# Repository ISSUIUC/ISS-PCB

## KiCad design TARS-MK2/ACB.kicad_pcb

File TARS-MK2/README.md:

# TARS-MK2

> Don't let me leave Murph!\
> -Matthew McConaughey

# TODO

## FCB:
- [ ] Finalize overall component locations and begin trace layout
- [ ] Add RFM95!
- [ ] Make appropriate connections to b2b (board-to-board) MLPlus connectors
- [x] Copy MCU_AC design to MCU_HYBRID
- [ ] Add connectors for pressure transducers (MPLUS 3pos?)

TODO for the MCU specifically:
- [x] Associate certain MIMX pins with T4.1 pins so connections match with MK1 design
- [ ] think about pull-up/down resistors on communication busses
- [ ] add test points for power-up sequence observation (for debugging)
- [ ] Think about MCU-MCU communication lines
- [ ] Figure out exactly which peripherals are available with chip-on-board that weren't on the T4.1
- [ ] Add I2C/UART (+SPI?) expansion ports
- [ ] Should MCUs be powered by 3V3 or 5V?
- [ ] SAM-M8Q?
- [x] Additional IMU? (Maybe MPU9250 or BMI160 look nice)

TODO for MPU:
- [x] Talk to Octavo systems and see if they can review our design on short notice
- [ ] Implement the boot configuration pins according the to C-SiP design manual
- [ ] Break out necessary I2C and SPI busses
- [x] Keep USB host connector (probably not)

## ACB:
  - [ ] Attempt to replace the SODIMM connector with a lower profile one
  - [ ] Add debug LEDS
  - [ ] Add UART port for console and debugging

## POWER:
  - [ ] Add MLPlus b2b connectors
  - [ ] Power ON LEDs!!
  - [ ] Add a ground plane (both sides)
  - [ ] Consider switching SMD footprints for mosfet and voltage regulator
  - [ ] Are XT60s going to fit (switch to XT30s? JST-XH?)

## COTS:
  - [x] Finalize layout of components.
  - [x] Add MLPlus b2b connectors
  - [x] Add MLPlus ejection charge/switch connectors

---

### Schematic Hierarchy:
- `TARS-MK2.sch`: Consolidated root schematic
  - `Power.sch`: Power management and charging schematic
    - In redesign
  - `COTS.sch`: Commercial altimeter system schematic
    - flight critical
  - `ACB.sch`: Advanced computation board schematic
    - extra fun stuff
  - `FCB.sch`: Flight computation board schematic
    - mission critical flight computers
    - `MPU.sch`: Microprocessor unit sub-schematic
        - copied from the PocketBeagle
    - `MCU_AC.sch`: Active Control Microcontroller unit sub-schematic
        - copied from the Teensy 4.1
    - `MCU_HYBRID.sch`: Hybrid Microcontroller unit sub-schematic
        - copied from the Teensy 4.1

### Some notes:
- Create 4 different schematic files (one for each board), and unify them through one parent
- Use **MPU** to refer to the **PocketBeagle**, **MCU** to refer to the **Teensy 4.1**
- Import all libraries into the `./libs` directory for each component used

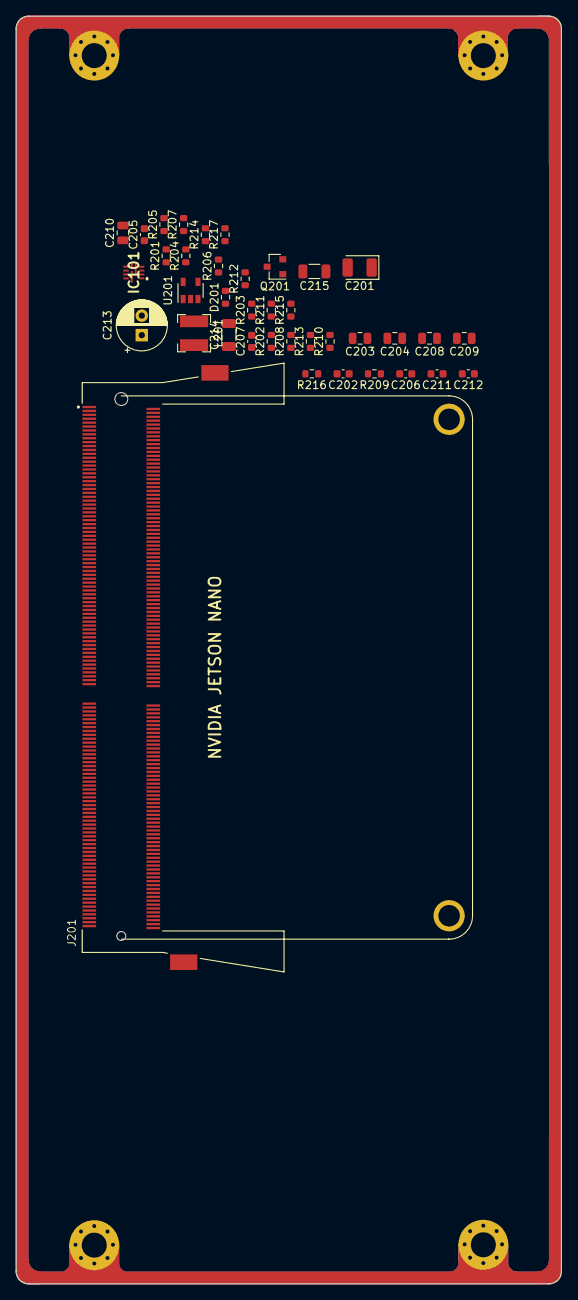
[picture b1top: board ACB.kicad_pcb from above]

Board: 2 copper layers, 69.9 x 162.4 mm, 38 parts (0 on the bottom side), 29 nets, no tracks yet.

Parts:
C201: 100uF; CP_EIA-3528-12_Kemet-T
C202: 0.1uF; C_0603_1608Metric
C203, C204, C208, C209, C210: 22uF; C_0805_2012Metric
C205, C206, C211, C212: 1uF; C_0603_1608Metric
C207: 33pF; C_0603_1608Metric
C213: 560uF; CP_Radial_D6.3mm_P2.50mm
C214, C215: 100uF; C_1206_3216Metric
D201: Green; R_0603_1608Metric
IC101: MP2384GG-P; MP2384GGP
J201: 2309413-1; Jetson_Nano
L201: 2.2uH; L_Bourns-SRN4018
Q201: DMN2230U; SOT-23
R201, R209: 10K; R_0603_1608Metric
R202, R203, R204, R205, R206, R212: 0; R_0603_1608Metric
R207: 40.2K; R_0603_1608Metric
R208: 8.87K; R_0603_1608Metric
R210, R211, R213, R215, R216, R217: 47K; R_0603_1608Metric
R214: 1.8K; R_0603_1608Metric
U201: TLV70018_SOT23-5; SOT-23-5

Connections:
/3V3_IO_PG: IC101.5, IC101.11, R201.2, U201.3
/CAM_I2C_SCL: J201.213, R216.2
/CAM_I2C_SDA: J201.215, R217.2
/I2C0_SCL: J201.185, R210.2
/I2C0_SDA: J201.187, R211.2
/I2C1_SCL: J201.189, R213.2
/I2C1_SDA: J201.191, R215.2
/PWR_BTN: J201.240, R209.2
/PWR_LED_CTRL: J201.127, R212.1
/SPI0_CS0: J201.95, J201.110
/SPI0_CS1: J201.97, J201.112
/SPI0_MISO: J201.93, J201.108
/SPI0_MOSI: J201.89, J201.104
/SPI0_SCK: J201.91, J201.106
/VDD_1V8: C212.1, U201.5
/VDD_3V3_SYS: C208.1, C209.1, C210.1, C211.1, L201.2, R201.1, R206.1, R210.1, R211.1, R213.1, R215.1, R216.1, R217.1, U201.1
/VDD_5V_IN: C201.1, C202.1, C203.1, C204.1, C213.1, C214.1, C215.1, D201.2, IC101.1, J201.251, J201.252, J201.253, J201.254, J201.255, J201.256, J201.257, J201.258, J201.259, J201.260, R209.1
GND: C201.2, C202.2, C203.2, C204.2, C205.2, C208.2, C209.2, C210.2, C211.2, C212.2, C213.2, C214.2, C215.2, IC101.2, IC101.3, IC101.4, IC101.9, J201.1, J201.2, J201.7, J201.8, J201.13, J201.14, J201.19, J201.20, J201.25, J201.26, J201.31, J201.32, J201.37, J201.38, J201.43, J201.44, J201.49, J201.50, J201.55, J201.56, J201.61, J201.62, J201.67, J201.68, J201.73, J201.74, J201.79, J201.80, J201.85, J201.86, J201.102, J201.107, J201.113, J201.119, J201.125, J201.129, J201.132, J201.135, J201.138, J201.141, J201.144, J201.146, J201.147, J201.152, J201.153, J201.158, J201.159, J201.164, J201.165, J201.170, J201.171, J201.176, J201.177, J201.200, J201.201, J201.217, J201.231, J201.241, J201.242, J201.243, J201.244, J201.245, J201.246, J201.247, J201.248, J201.249, J201.250, J201.S1, J201.S2, Q201.2, R208.2, U201.2
unnamed: C205.1, IC101.8
unnamed: C206.1, R202.2
unnamed: C206.2, IC101.6, L201.1, R203.1
unnamed: C207.1, R203.2, R205.1
unnamed: C207.2, R206.2, R207.1
unnamed: D201.1, R214.1
unnamed: IC101.7, R202.1
unnamed: IC101.10, R204.1
unnamed: Q201.1, R212.2
unnamed: Q201.3, R214.2
unnamed: R204.2, R205.2, R207.2, R208.1

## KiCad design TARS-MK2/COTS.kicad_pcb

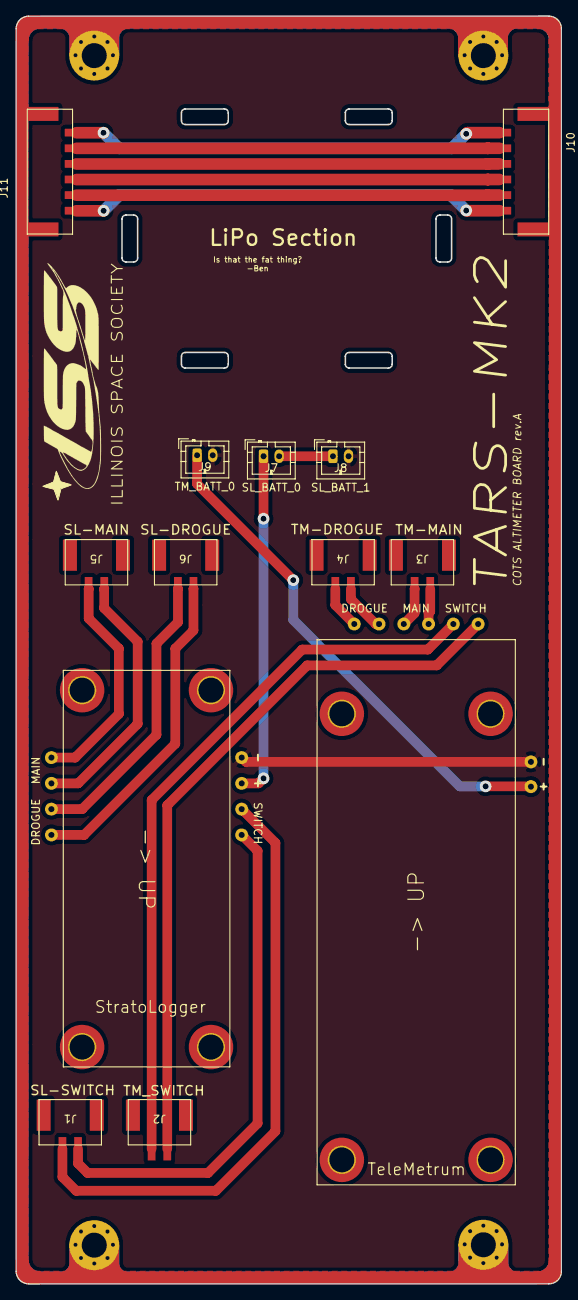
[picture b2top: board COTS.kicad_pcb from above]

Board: 2 copper layers, 69.9 x 162.4 mm, 13 parts (0 on the bottom side), 22 nets.

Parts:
A1: StratoLogger
A2: TeleMetrum
J1: SL-SWITCH; 505575-0271
J2: TM_SWITCH; 505575-0271
J3: TM-MAIN; 505575-0271
J4: TM-DROGUE; 505575-0271
J5: SL-MAIN; 505575-0271
J6: SL-DROGUE; 505575-0271
J7: SL_BATT_0; JST_PH_B2B-PH-K_1x02_P2.00mm_Vertical
J8: SL_BATT_1; JST_PH_B2B-PH-K_1x02_P2.00mm_Vertical
J9: TM_BATT_0; JST_PH_B2B-PH-K_1x02_P2.00mm_Vertical
J10, J11: 505578-0671

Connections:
unnamed: A1.1, J1.2
unnamed: A1.2, J1.1
unnamed: A1.5, J6.2
unnamed: A1.6, J6.1
unnamed: A1.7, J5.2
unnamed: A1.8, J5.1
unnamed: A2.3, J2.2
unnamed: A2.4, J2.1
unnamed: A2.5, J3.2
unnamed: A2.6, J3.1
unnamed: A2.7, J4.2
unnamed: A2.8, J4.1
unnamed: J7.2, J8.1
unnamed: J10.1, J11.6
unnamed: J10.2, J11.5
unnamed: J10.3, J11.4
unnamed: J10.4, J11.3
unnamed: J10.5, J11.2
unnamed: J10.6, J11.1
SL_POWER_NEGATIVE: A1.4, A2.2, J8.2, J9.2
SL_POWER_POSITIVE: A1.3, J7.1
TM_POWER_POSITIVE: A2.1, J9.1

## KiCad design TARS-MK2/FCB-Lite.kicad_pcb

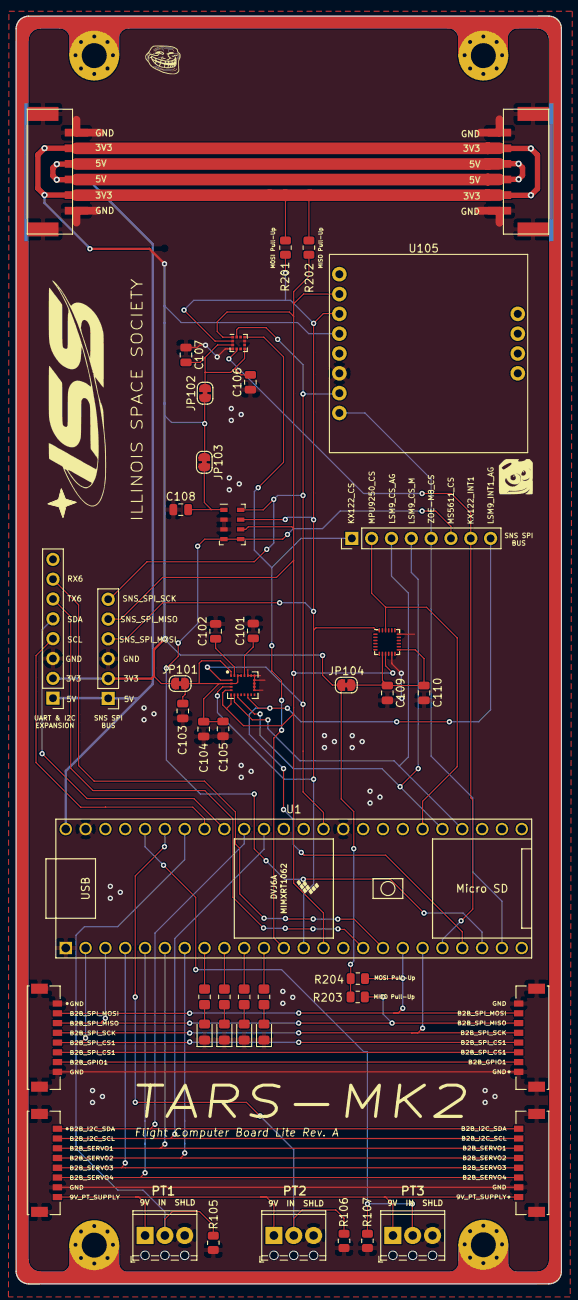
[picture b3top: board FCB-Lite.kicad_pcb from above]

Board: 2 copper layers, 69.9 x 162.4 mm, 47 parts (0 on the bottom side), 48 nets.

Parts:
C101: 10 nF; C_0805_2012Metric
C102, C103, C104, C106, C107, C108, C109, C110: 100 nF; C_0805_2012Metric
C105: 10 uF; C_0805_2012Metric
D9001, D9002, D9003, D9004: LED; LED_0805_2012Metric_Pad1.15x1.40mm_HandSolder
J101, J102, J105, J106: 505567-0871; MOLEX_505567-0871
J103, J104: 505578-0671
J107: PT1; TerminalBlock_Phoenix_MPT-0,5-3-2.54_1x03_P2.54mm_Horizontal
J108: PT2; TerminalBlock_Phoenix_MPT-0,5-3-2.54_1x03_P2.54mm_Horizontal
J109: PT3; TerminalBlock_Phoenix_MPT-0,5-3-2.54_1x03_P2.54mm_Horizontal
J201: Conn_01x06_Male; PinHeader_1x06_P2.54mm_Vertical
J202, J203: Conn_01x08_Male; PinHeader_1x08_P2.54mm_Vertical
JP101, JP102, JP103, JP104: Jumper_NC_Small; SolderJumper-2_P1.3mm_Bridged_RoundedPad1.0x1.5mm
R105, R106, R107: 150; R_0805_2012Metric
R201, R202, R203, R204: R_US; R_0805_2012Metric
R9001, R9002, R9003, R9004: 470; R_0805_2012Metric_Pad1.20x1.40mm_HandSolder
U1: Teensy4.1_bare; Teensy41_bare
U101: LSM9DS1; LGA-24L_3x3.5mm_P0.43mm
U102: KX122-1042; LGA-12_2x2mm_P0.5mm
U103: MS5611-01BA; LGA-8_3x5mm_P1.25mm
U104: MPU-9250; InvenSense_QFN-24_3x3mm_P0.4mm
U105: ZOE-MQ8-BREAKOUT; ZOE-M8QBRKT

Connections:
/3V3: J103.2, J103.5, J104.2, J104.5, J201.2, J203.2, JP101.1, JP102.1, JP103.1, JP104.1, R201.1, R202.1, R203.1, R204.1, U105.4
/5V: J103.3, J103.4, J104.3, J104.4, J201.1, J203.1, U1.48
/9V_PT_SUPPLY: J102.8, J106.1, J107.1, J108.1, J109.1
/B2B_GPIO1: J101.7, J105.2
/B2B_I2C_SCL: J102.2, J106.7, U1.38
/B2B_I2C_SDA: J102.1, J106.8, U1.39
/B2B_SERVO1: J102.3, J106.6, U1.6
/B2B_SERVO2: J102.4, J106.5, U1.7
/B2B_SERVO3: J102.5, J106.4, U1.4
/B2B_SERVO4: J102.6, J106.3, U1.5
/B2B_SPI_CS1: J101.5, J105.4, U1.2
/B2B_SPI_CS2: J101.6, J105.3
/B2B_SPI_MISO: J101.3, J105.6, R203.2, U1.3
/B2B_SPI_MOSI: J101.2, J105.7, R204.2, U1.18
/B2B_SPI_SCK: J101.4, J105.5, U1.19
/I2C_SCL: J203.4, U1.41
/I2C_SDA: J203.5, U1.40
/KX122_CS: J202.1, U1.12, U102.10
/KX122_INT1: J202.7, U1.20, U102.5
/LSM9_CS_AG: J202.3, U1.28, U101.7
/LSM9_CS_M: J202.4, U1.29, U101.8
/LSM9_INT1_AG: J202.8, U1.21, U101.11
/MPU9250_CS: J202.2, U1.30, U104.22
/MS5611_CS: J202.6, U1.22, U103.4, U103.5
/PT1: J107.2, R105.1, U1.42
/PT2: J108.2, R106.1, U1.43
/PT3: J109.2, R107.1, U1.44
/SNS_SPI_MISO: J201.5, R201.2, U1.14, U101.5, U101.6, U102.1, U103.6, U104.9, U105.2
/SNS_SPI_MOSI: J201.4, R202.2, U1.13, U101.4, U102.2, U103.7, U104.24, U105.3
/SNS_SPI_SCK: J201.6, U1.35, U101.2, U102.12, U103.8, U105.7
/UART_RX6: J203.7, U1.17
/UART_TX6: J203.6, U1.16
/ZOE_MQ8_BRKT_CS: J202.5, U1.23, U105.8
GND: C101.2, C102.2, C103.2, C104.2, C105.2, C106.1, C107.1, C108.1, C109.2, C110.1, D9001.1, D9002.1, D9003.1, D9004.1, J101.1, J101.8, J101.P1, J101.P2, J102.7, J102.P1, J102.P2, J103.1, J103.6, J103.P1, J103.P2, J104.1, J104.6, J104.P1, J104.P2, J105.1, J105.8, J105.P1, J105.P2, J106.2, J106.P1, J106.P2, J107.3, J108.3, J109.3, J201.3, J203.3, R105.2, R106.2, R107.2, U1.1, U1.34, U1.47, U101.14, U101.15, U101.16, U101.17, U101.18, U101.19, U101.20, U102.4, U102.9, U103.2, U103.3, U104.11, U104.18, U105.6
unnamed: C101.1, U101.21
unnamed: C102.1, U101.24
unnamed: C103.1, C104.1, C105.1, JP101.2, U101.1, U101.3, U101.22, U101.23
unnamed: C106.2, C107.2, JP102.2, U102.3, U102.7
unnamed: C108.2, JP103.2, U103.1
unnamed: C109.1, C110.2, JP104.2, U104.8, U104.13
unnamed: D9001.2, R9001.2
unnamed: D9002.2, R9002.2
unnamed: D9003.2, R9003.2
unnamed: D9004.2, R9004.2
unnamed: R9001.1, U1.8
unnamed: R9002.1, U1.9
unnamed: R9003.1, U1.10
unnamed: R9004.1, U1.11

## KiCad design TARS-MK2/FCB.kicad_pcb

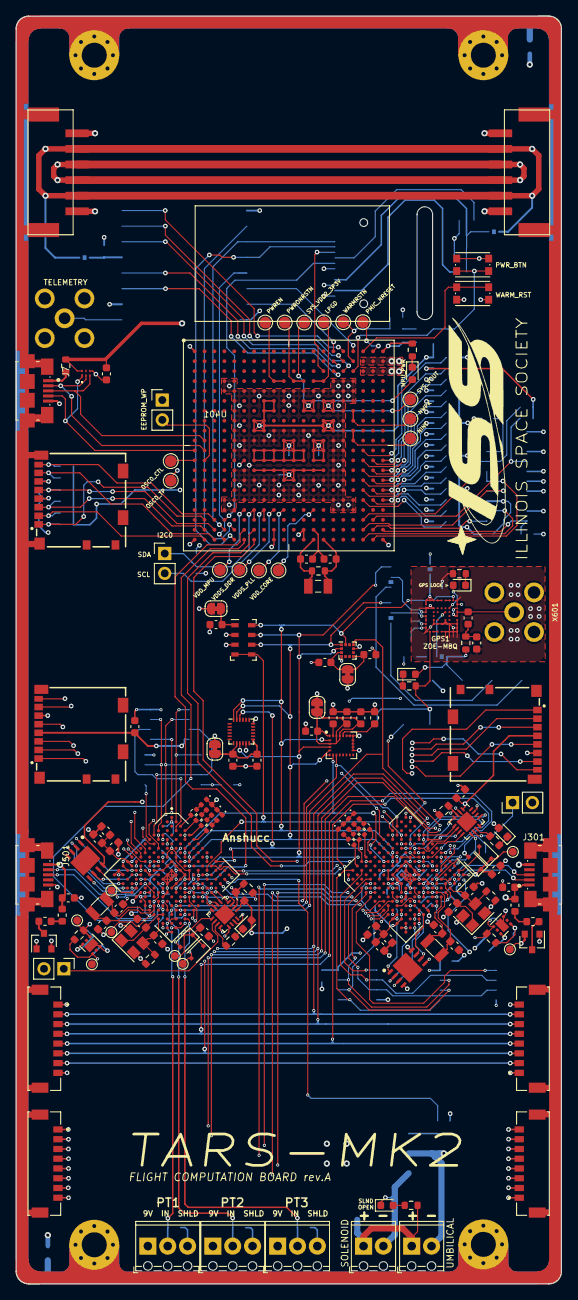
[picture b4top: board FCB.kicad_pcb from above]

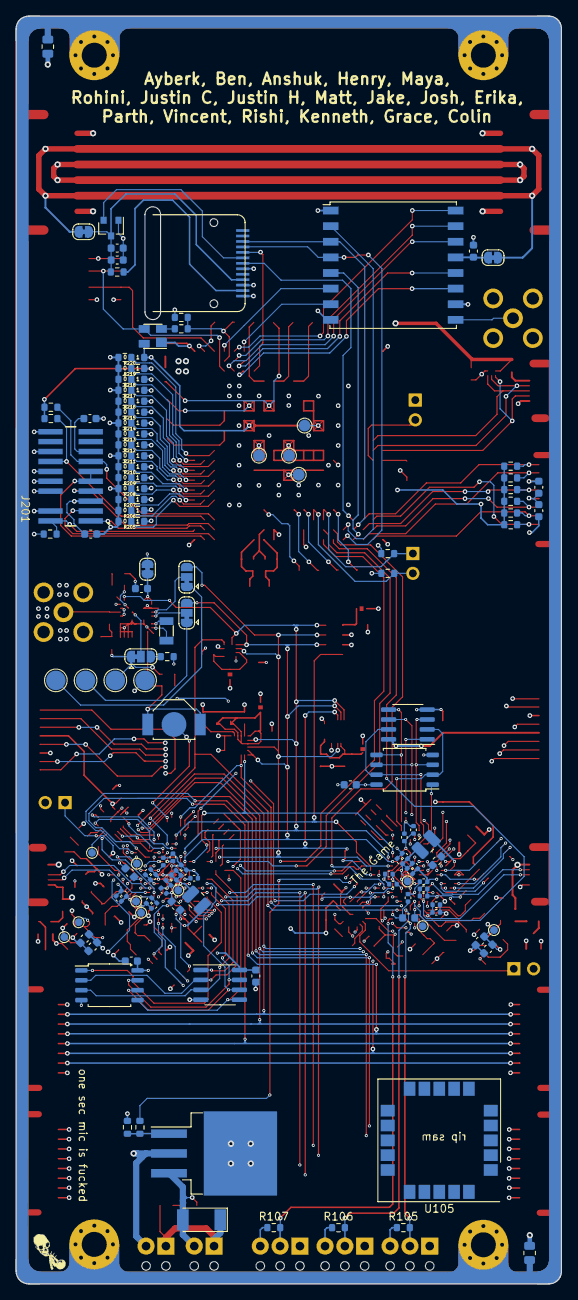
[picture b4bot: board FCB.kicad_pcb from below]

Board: 4 copper layers, 69.9 x 162.4 mm, 280 parts (124 on the bottom side), 262 nets.

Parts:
BT601: BK-414; BAT_BK-414
C1, C2: 0.1uF, 10V; C_0603_1608Metric
C3: 0.1uF, 6.3V; C_0603_1608Metric
C101: 10 nF; C_0603_1608Metric
C102, C103, C104, C106, C107, C108, C109, C110: 100 nF; C_0603_1608Metric
C105: 10 uF; C_0603_1608Metric
C111: 100nF; C_0603_1608Metric
C112, C332, C532: 10uF; C_0603_1608Metric
C113: 1uF; C_0603_1608Metric
C201, C202, C601: 0.1uF; C_0603_1608Metric
C203, C204: 18pF, 50V; C_0603_1608Metric
C301, C302, C501, C502: 12pF; C_0603_1608Metric
C303, C304, C503, C504: 20pF; C_0603_1608Metric
C305, C306, C505, C506: 10nF; C_0402_1005Metric
C308, C309, C313, C315, C318, C319, C320, C321, C508, C509, C513, C515, C518, C519, C520, C521: 0.22uF; C_0603_1608Metric
C311, C312, C314, C316, C317, C511, C512, C514, C516, C517: 0.22uF; C_0402_1005Metric
C322, C323, C325, C326, C522, C523, C525, C526: 4.7uF; C_0402_1005Metric
C324, C524: 4.7uF; C_0603_1608Metric
C327, C527: 2.2uF; C_0603_1608Metric
C328, C528: 2.2uF; C_0402_1005Metric
C330, C331, C530, C531: 10uF; C_0402_1005Metric
C602: 47pF; C_0603_1608Metric
D1: PWR; LED_0603_1608Metric
D101: SLND_OPEN; LED_0603_1608Metric
D102: SM4002; D_MELF
D103, D104, D105, D106, D107, D108, D109, D110: LED; LED_0402_1005Metric
D301, D302, D501, D502: BAT54J; D_SOD-323F
D304, D504, D602: LED; LED_0603_1608Metric
D601: 0.5A/40V/420mV; D_0603_1608Metric
DISP1: DISP_LCD_GENERIC_SPI_1.14IN_240X135_WRAPUNDER; TFT_1.14IN_240X135_CUTOUT
F301, F501: 500mA; Fuse_0603_1608Metric
FB601: 120; L_0603_1608Metric
IC1: TPD4S012DRYR
IC101: AXP083-SAG; SOT-23
J4: I2C0; PinHeader_1x02_P2.54mm_Vertical
J6: EEPROM_WP; PinHeader_1x02_P2.54mm_Vertical
J7, J301, J501: 10118192-0001LF; AMPHENOL_10118192-0001LF
J101, J102, J103, J104: 505567-0871; MOLEX_505567-0871
J105, J106: 505578-0671
J107: PT1; TerminalBlock_Phoenix_MPT-0,5-3-2.54_1x03_P2.54mm_Horizontal
J108: PT2; TerminalBlock_Phoenix_MPT-0,5-3-2.54_1x03_P2.54mm_Horizontal
J109: PT3; TerminalBlock_Phoenix_MPT-0,5-3-2.54_1x03_P2.54mm_Horizontal
J110: SLND; TerminalBlock_Phoenix_MPT-0,5-2-2.54_1x02_P2.54mm_Horizontal
J111: UMBLCL; TerminalBlock_Phoenix_MPT-0,5-2-2.54_1x02_P2.54mm_Horizontal
J201: FTR-110-03-G-D-06; SAMTEC_FTR-110-03-G-D-06
J302, J502, J5000: Micro_SD_Card; NEW_1040310811
J306, J506: Conn_01x02; PinHeader_1x02_P2.54mm_Vertical
JP101, JP102, JP103, JP104, JP106, JP601: Jumper_NC_Small; SolderJumper-2_P1.3mm_Bridged_RoundedPad1.0x1.5mm
JP105: TLM_JPR; SolderJumper-2_P1.3mm_Bridged_RoundedPad1.0x1.5mm
JP602, JP605, JP606: D_SEL; SolderJumper-3_P1.3mm_Bridged12_RoundedPad1.0x1.5mm
L301, L501: 4.7uH; L_1008_2520Metric
L302, L303, L502, L503: 120; L_0603_1608Metric
Q101: IRLZ44N; TO-263-3_TabPin2
Q301, Q501: DG2305UX; SOT-23
R1: 1K; R_0603_1608Metric
R2, R3, R4, R5, R6, R7: 10K; R_0603_1608Metric
R8: 0; R_0603_1608Metric
R101: 22; R_0603_1608Metric
R102, R104, R503: 1k; R_0603_1608Metric
R103: 10k; R_0603_1608Metric
R105, R106, R107: 150; R_0603_1608Metric
R108, R109, R110, R111, R112, R113, R114, R115: 470; R_0402_1005Metric
R201, R202, R203: 4.75K, 1%; R_0603_1608Metric
R204: 1M; R_0603_1608Metric
R205, R206, R207, R209, R219: 100K; R_0603_3WAY_12
R208, R210, R211, R212, R213, R214, R215, R216, R217, R218, R220: 100K; R_0603_3WAY_23
R302, R502: 470; R_0603_1608Metric
R305, R505: 2.2M; R_0603_1608Metric
R306, R307, R506, R507: 100K; R_0603_1608Metric
R501, R602: 100k; R_0603_1608Metric
R504, R508: 1.5k; R_0603_1608Metric
R601: 3.3k; R_0603_1608Metric
R603: 330; R_0603_1608Metric
R604: 10; R_0603_1608Metric
R998, R999: 0.1; R_0805_2012Metric
SW501: WARM_RST; SW_Push_1P1T_NO_CK_KMR2
SW502: PMIC_PB; SW_Push_1P1T_NO_CK_KMR2
TP1: WARMRSTN; TestPoint_Pad_D1.5mm
TP2: PWREN; TestPoint_Pad_D1.5mm
TP3: LPGD; TestPoint_Pad_D1.5mm
TP4: NWPK; TestPoint_Pad_D1.5mm
TP5: NINT; TestPoint_Pad_D1.5mm
TP6: PWRONRSTN; TestPoint_Pad_D1.5mm
TP7: VDD_MPU; TestPoint_Pad_D1.5mm
TP8: VDDS_DDR; TestPoint_Pad_D1.5mm
TP9: VDDS_PLL; TestPoint_Pad_D1.5mm
TP10: VDD_CORE; TestPoint_Pad_D1.5mm
TP11: OSCO_TP; TestPoint_Pad_D1.5mm
TP12: SYS_VOUT; TestPoint_Pad_D1.5mm
TP13: SYS_VDD1_3P3V; TestPoint_Pad_D1.5mm
TP14: SYS_VDD2_3P3V; TestPoint_Pad_D1.5mm
TP15: SYS_VDD3_3P3V; TestPoint_Pad_D1.5mm
TP16: SYS_VDD_1P8V; TestPoint_Pad_D1.5mm
TP17: SYS_RTC_1P8V; TestPoint_Pad_D1.5mm
TP18: PMIC_NRESET; TestPoint_Pad_D1.5mm
TP201: OSC0_CTL; TestPoint_Pad_D1.5mm
TP301, TP501: USB_VBUS; TestPoint_Pad_D1.0mm
TP302, TP502: VDD_USB_CAP; TestPoint_Pad_D1.0mm
TP303, TP503: VDD_SNVS_IN; TestPoint_Pad_D1.0mm
TP304, TP504: VDD_SNVS_CAP; TestPoint_Pad_D1.0mm
TP305, TP505: NVCC_PLL; TestPoint_Pad_D1.0mm
TP306, TP506: VDD_HIGH_CAP; TestPoint_Pad_D1.0mm
TP307, TP507: REG_EN; TestPoint_Pad_D1.0mm
TP308, TP508: VDD_HIGH_IN; TestPoint_Pad_D1.0mm
TP309, TP509: VDD_SOC_IN; TestPoint_Pad_D1.0mm
TP601: 3V3_UART; TestPoint_Pad_D2.5mm
TP602: UART_TXD; TestPoint_Pad_D2.5mm
TP603: UART_RXD; TestPoint_Pad_D2.5mm
TP604: GND; TestPoint_Pad_D2.5mm
U1: APX811-31UGSOT; SOT-143
U101: LSM9DS1; LGA-24L_3x3.5mm_P0.43mm
U102: KX122-1711; LGA-12_2x2mm_P0.5mm
U103: MS5611-01BA; LGA-8_3x5mm_P1.25mm
U104: MPU-9250; InvenSense_QFN-24_3x3mm_P0.4mm
U105: ublox_SAM-M8Q
U106: RFM95W-915S2; HOPERF_RFM9XW_SMD
U301, U501: MIMXRT1xxxxVJ; BGA-196_14x14_12.0x12.0mm
U302, U502: MKL02Z32VFG4; QFN-16-1EP_3x3mm_P0.5mm_EP1.9x1.9mm
U303, U503: W25Q64JVXGIM_TR; W25Q64JVXGIM
U304, U504: ESP-PSRAM32; SOIC-8_3.9x4.9mm_P1.27mm
U305, U505: TLV75733PDRV; WSON-6-1EP_2x2mm_P0.65mm_EP1x1.6mm
U306, U506: W25Q128JVS; SOIC-8_5.23x5.23mm_P1.27mm
U401: OSD3358-512M-BCB; OSD335X-BGA-400
U601: ZOE-M8Q; ZOE-M8
X101: SMA; SMA90_DIP
X601: SMACONNECTOR; SMA90_DIP
Y201: ABS07-32.768KHZ-T; XTAL_ABS07-32.768KHZ-T
Y301, Y501: 24 MHz; Crystal_SMD_3225-4Pin_3.2x2.5mm
Y302, Y502: 32.768 kHz; Crystal_SMD_3215-2Pin_3.2x1.5mm
Y601: 32.768kHz; Crystal_SMD_3215-2Pin_3.2x1.5mm

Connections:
/3V3: J105.2, J105.5, J106.2, J106.5, JP101.1, JP102.1, JP103.1, JP104.1, JP105.2, JP106.1, JP601.1
/5V: C327.1, C527.1, F301.2, F501.2, J105.3, J105.4, J106.3, J106.4, J301.1, J501.1, U401.C18, U401.C19, U401.C20
/9V_PT_SUPPLY: J102.8, J103.1, J107.1, J108.1, J109.1
/B2B_GPIO1: J101.7, J104.2
/B2B_I2C_SCL: J102.2, J103.7, U301.J11, U501.J11
/B2B_I2C_SDA: J102.1, J103.8, U301.K11, U501.K11
/B2B_SERVO1: J102.3, J103.6, U301.F2, U501.F2
/B2B_SERVO2: J102.4, J103.5, U301.G5, U501.G5
/B2B_SERVO3: J102.5, J103.4, U301.H5, U501.H5
/B2B_SERVO4: J102.6, J103.3, U301.H4, U501.H4
/B2B_SPI_CS1: J101.5, J104.4, U301.H12
/B2B_SPI_CS2: J101.6, J104.3, U501.H12
/B2B_SPI_MISO: J101.3, J104.6, U301.H11, U501.H11
/B2B_SPI_MOSI: J101.2, J104.7, U301.G12, U501.G12
/B2B_SPI_SCK: J101.4, J104.5, U301.J14, U501.J14
/INTER_MCU_UART_RX: U301.A11, U501.B11
/INTER_MCU_UART_TX: U301.B11, U501.A11
/KX122_CS: U102.10, U301.L12, U501.L12
/LCD_CS: DISP1.7, U401.V4
/LCD_DC: DISP1.5, U401.C14
/LCD_RST: DISP1.6, IC101.2
/LSM9_CS_AG: U101.7, U301.D7, U501.D7
/LSM9_CS_M: U101.8, U301.A12, U501.K12
/MCU_AC/3V3_MCU: C306.1, C308.1, C311.1, C320.2, C321.2, C323.1, C328.1, D302.2, D304.2, J302.4, L303.1, R307.1, TP308.1, U301.E6, U301.E9, U301.F5, U301.F10, U301.J6, U301.J10, U301.K4, U301.K5, U301.N14, U301.P12, U302.1, U303.8, U304.8, U305.1, U306.8
/MCU_AC/AD_B0_04: U301.F11, U302.4
/MCU_AC/AD_B0_06: U301.E14, U302.5
/MCU_AC/AD_B0_07: U301.F12, U302.8
/MCU_AC/AD_B0_08: U301.F13, U302.13
/MCU_AC/AD_B0_09: U301.F14, U302.7
/MCU_AC/AD_B0_10: U301.G13, U302.6
/MCU_AC/AD_B0_11: R306.1, U301.G10, U301.K3, U302.3
/MCU_AC/B0_13: U301.D10, U302.12
/MCU_AC/EMC_22: U301.F1, U306.1
/MCU_AC/EMC_24: U301.D3, U304.1
/MCU_AC/EMC_25: U301.D2, U304.6, U306.6
/MCU_AC/EMC_26: U301.B3, U304.2, U306.2
/MCU_AC/EMC_27: U301.A2, U304.5, U306.5
/MCU_AC/EMC_28: U301.D1, U304.3, U306.3
/MCU_AC/EMC_29: U301.E1, U304.7, U306.7
/MCU_AC/POR_B: U301.M7, U302.9
/MCU_AC_LED_BLUE: R113.2, U301.A6
/MCU_AC_LED_ORANGE: R112.2, U301.A5
/MCU_AC_LED_RED: R115.2, U301.A4
/MCU_AC_LED_WHITE: R111.2, U301.A3
/MCU_AC_SPI2_MOSI: U301.F3, U302.15
/MCU_AC_UART1_RX: U301.G11, U401.W7
/MCU_AC__UART1_TX: U301.M11, U401.Y7
/MCU_HYBRID/3V3_MCU: C506.1, C508.1, C511.1, C520.2, C521.2, C523.1, C528.1, D502.2, D504.2, J502.4, L503.1, R507.1, TP508.1, U501.E6, U501.E9, U501.F5, U501.F10, U501.J6, U501.J10, U501.K4, U501.K5, U501.N14, U501.P12, U502.1, U503.8, U504.8, U505.1, U506.8
/MCU_HYBRID/AD_B0_04: U501.F11, U502.4
/MCU_HYBRID/AD_B0_06: U501.E14, U502.5
/MCU_HYBRID/AD_B0_07: U501.F12, U502.8
/MCU_HYBRID/AD_B0_08: U501.F13, U502.13
/MCU_HYBRID/AD_B0_09: U501.F14, U502.7
/MCU_HYBRID/AD_B0_10: U501.G13, U502.6
/MCU_HYBRID/AD_B0_11: R506.1, U501.G10, U501.K3, U502.3
/MCU_HYBRID/B0_13: U501.D10, U502.12
/MCU_HYBRID/EMC_22: U501.F1, U506.1
/MCU_HYBRID/EMC_24: U501.D3, U504.1
/MCU_HYBRID/EMC_25: U501.D2, U504.6, U506.6
/MCU_HYBRID/EMC_26: U501.B3, U504.2, U506.2
/MCU_HYBRID/EMC_27: U501.A2, U504.5, U506.5
/MCU_HYBRID/EMC_28: U501.D1, U504.3, U506.3
/MCU_HYBRID/EMC_29: U501.E1, U504.7, U506.7
/MCU_HYBRID/POR_B: U501.M7, U502.9
/MCU_HYB_LED_BLUE: R110.2, U501.A6
/MCU_HYB_LED_ORANGE: R109.2, U501.A5
/MCU_HYB_LED_RED: R114.2, U501.A4
/MCU_HYB_LED_WHITE: R108.2, U501.A3
/MCU_HYB_SPI2_MOSI: U501.F3, U502.15
/MCU_HYB_UART1_RX: U401.W6, U501.G11
/MCU_HYB_UART1_TX: U401.Y6, U501.M11
/MPU9250_CS: U104.22, U301.D11, U501.D11
/MPU/JTAG_EMU0: J201.13, R201.2, U401.V18
/MPU/JTAG_EMU1: J201.14, R203.1, U401.V19
/MPU/JTAG_TCK: J201.09, J201.11, U401.Y19
/MPU/JTAG_TDI: J201.03, U401.Y18
/MPU/JTAG_TDO: J201.07, U401.W18
/MPU/JTAG_TMS: J201.01, U401.W19
/MPU/JTAG_TRSTN: J201.02, R202.1, U401.W20
/MPU/MMC0_CLK: J5000.5, R4.2, U401.W3
/MPU/MMC0_CMD: J5000.3, R5.2, U401.W2
/MPU/MMC0_DAT0: J5000.7, R3.2, U401.Y3
/MPU/MMC0_DAT1: J5000.8, R2.2, U401.V3
/MPU/MMC0_DAT2: J5000.1, R7.2, U401.V2
/MPU/MMC0_DAT3: J5000.2, R6.2, U401.Y2
/MPU/SYS_RESETN: C201.1, J201.15
/MPU/SYS_RTC_1P8V: TP17.1, U401.K13, U401.K14, U401.L13, U401.L14, U401.M13, U401.M14
/MPU/SYS_VDD1_3P3V: C202.1, J201.05, R201.1, R203.2, R205.1, R206.1, R207.1, R208.1, R209.1, R210.1, R211.1, R212.1, R213.1, R214.1, R215.1, R216.1, R217.1, R218.1, R219.1, R220.1, R504.1, R508.1, TP13.1, U1.4, U401.F8, U401.F9, U401.G8, U401.G9, U401.H7, U401.H8, U401.H14, U401.H15, U401.J7, U401.J8, U401.J14, U401.J15
/MPU/SYS_VDD2_3P3V: D1.2, TP14.1, U401.F12, U401.F13, U401.G12, U401.G13
/MPU/SYS_VDD3_3P3V: C1.1, C2.1, J5000.4, R2.1, R3.1, R4.1, R5.1, R6.1, R7.1, TP15.1, U401.K10, U401.K11, U401.L7, U401.L8, U401.L9, U401.L10, U401.L11, U401.L12, U401.M7, U401.M8, U401.M9, U401.M10, U401.M11, U401.M12
/MPU/SYS_VDD_1P8V: TP16.1, U401.N7, U401.N8, U401.N9, U401.N10, U401.N11, U401.N12, U401.N13, U401.N14, U401.P10, U401.P11, U401.W12, U401.Y12
/MPU/SYS_VOUT: TP12.1, U401.F14, U401.F15, U401.G14, U401.G15
/MPU/USB0_DM: IC1.3, J7.3, U401.K2
/MPU/USB0_DP: IC1.2, J7.2, U401.L2
/MPU/USB0_ID: IC1.1, J7.4, U401.L1
/MPU/USB5V: C3.1, IC1.6, R8.1, U401.B18, U401.B19, U401.B20
/MPU_SPI0_MISO: U106.2, U401.W5
/MPU_SPI0_MOSI: DISP1.3, U106.3, U401.W4
/MPU_SPI0_SCK: DISP1.4, U106.4, U401.Y5
/MS5611_CS: U103.4, U103.5, U301.C11, U501.C11
/PT1: J107.2, R105.2, U501.M13
/PT2: J108.2, R106.2, U501.M12
/PT3: J109.2, R107.2, U501.L14
/SLND_TRIG: R104.2, U301.B14, U501.B14
/SNS_SPI_MISO: JP605.3, U101.5, U101.6, U102.1, U103.6, U104.23, U301.E7, U501.E7
/SNS_SPI_MOSI: JP606.3, U101.4, U102.2, U103.7, U104.9, U301.E8, U501.E8
/SNS_SPI_SCK: U101.2, U102.12, U103.8, U104.24, U301.D8, U501.D8, U601.P$B1
/TLM_CS: U106.5, U401.Y4
/TLM_DIO0: U106.14, U401.C16
/TLM_DIO1: U106.15, U401.B16
/TLM_DIO2: U106.16, U401.A16
/TLM_DIO3: U106.11, U401.C15
/TLM_DIO4: U106.12, U401.B15
/TLM_DIO5: U106.7, U401.A15
/TLM_RST: U106.6, U401.A17
/ZOE-M8Q/3V3: C601.1, D601.2, JP601.2, JP602.1, R604.1, TP601.1, U601.P$G1, U601.P$H1, U601.P$J1, U601.P$J2
/ZOE-M8Q/UART_RXD: JP606.1, TP603.1
/ZOE-M8Q/UART_TXD: JP605.1, TP602.1
/ZOE-M8Q/VBATT: BT601.1+, BT601.2+, R601.2, U601.P$H9
/ZOE_CS: U301.A9, U501.C14, U601.P$A2
GND: BT601.-, C1.2, C2.2, C3.2, C101.1, C102.2, C103.2, C104.2, C105.2, C106.1, C107.1, C108.1, C109.1, C110.1, C111.2, C112.2, C113.2, C201.2, C202.2, C301.2, C302.2, C303.2, C304.2, C305.2, C306.2, C308.2, C309.2, C311.2, C312.2, C313.2, C314.2, C315.2, C316.2, C317.2, C318.2, C319.2, C320.1, C321.1, C322.2, C323.2, C324.2, C325.2, C326.2, C327.2, C328.2, C330.2, C331.2, C332.2, C501.2, C502.2, C503.2, C504.2, C505.2, C506.2, C508.2, C509.2, C511.2, C512.2, C513.2, C514.2, C515.2, C516.2, C517.2, C518.2, C519.2, C520.1, C521.1, C522.2, C523.2, C524.2, C525.2, C526.2, C527.2, C528.2, C530.2, C531.2, C532.2, C601.2, C602.2, D103.1, D104.1, D105.1, D106.1, D107.1, D108.1, D109.1, D110.1, DISP1.8, DISP1.11, DISP1.13, IC1.4, IC101.1, J6.1, J7.5, J101.1, J101.8, J102.7, J103.2, J104.1, J104.8, J105.1, J105.6, J106.1, J106.6, J107.3, J108.3, J109.3, J111.2, J201.04, J201.08, J201.10, J201.12, J201.16, J201.20, J301.5, J301.SH1, J301.SH2, J301.SH3, J301.SH4, J301.SH5, J301.SH6, J302.6, J306.2, J501.5, J501.SH1, J501.SH2, J501.SH3, J501.SH4, J501.SH5, J501.SH6, J502.6, J506.2, J5000.6, Q101.2, Q301.1, Q501.1, R1.2, R103.2, R105.1, R106.1, R107.1, R202.2, R205.3, R206.3, R207.3, R208.3, R209.3, R210.3, R211.3, R212.3, R213.3, R214.3, R215.3, R216.3, R217.3, R218.3, R219.3, R220.3, R305.1, R306.2, R501.1, R505.1, R506.2, R602.2, R603.2, R998.1, R999.1, SW501.1, SW502.1, TP604.1, U1.1, U101.14, U101.15, U101.16, U101.17, U101.18, U101.19, U101.20, U102.4, U102.9, U103.2, U103.3, U104.11, U104.18, U106.1, U106.8, U106.10, U301.A1, U301.A14, U301.B5, U301.B10, U301.E2, U301.E13, U301.G7, U301.G8, U301.H7, U301.H8, U301.J7, U301.J8, U301.K2, U301.K9, U301.K13, U301.L9, U301.N1, U301.N2, U301.N5, U301.N8, U301.P1, U301.P14, U302.2, U302.17, U303.4, U304.4, U305.3, U305.7, U306.4, U401.A1, U401.A20, U401.D4, U401.D5, U401.D15, U401.D16, U401.D17, U401.E4, U401.E5, U401.E6, U401.E7, U401.E8, U401.E9, U401.E10, U401.E11, U401.E12, U401.E13, U401.E14, U401.E15, U401.E16, U401.E17, U401.F5, U401.F10, U401.F11, U401.F16, U401.F17, U401.G5, U401.G16, U401.H5, U401.H16, U401.J5, U401.J9, U401.J10, U401.J11, U401.J12, U401.J13, U401.J16, U401.K5, U401.K6, U401.K7, U401.K8, U401.K9, U401.K12, U401.K15, U401.K16, U401.L5, U401.L6, U401.L15, U401.L16, U401.M5, U401.M15, U401.M16, U401.N5, U401.N6, U401.N15, U401.N16, U401.P5, U401.P6, U401.P7, U401.P8, U401.P9, U401.P12, U401.P13, U401.P14, U401.P15, U401.P16, U401.R5, U401.R9, U401.R10, U401.R11, U401.R12, U401.R16, U401.T4, U401.T5, U401.T6, U401.T7, U401.T8, U401.T9, U401.T10, U401.T11, U401.T12, U401.T13, U401.T14, U401.T15, U401.T16, U401.T17, U401.U4, U401.U5, U401.U15, U401.U16, U401.U17, U401.W9, U401.Y1, U401.Y9, U401.Y20, U501.A1, U501.A14, U501.B5, U501.B10, U501.E2, U501.E13, U501.G7, U501.G8, U501.H7, U501.H8, U501.J7, U501.J8, U501.K2, U501.K9, U501.K13, U501.L9, U501.N1, U501.N2, U501.N5, U501.N8, U501.P1, U501.P14, U502.2, U502.17, U503.4, U504.4, U505.3, U505.7, U506.4, U601.P$A1, U601.P$A3, U601.P$A5, U601.P$A7, U601.P$A8, U601.P$A9, U601.P$B9, U601.P$C7, U601.P$C9, U601.P$D6, U601.P$D9, U601.P$E7, U601.P$F7, U601.P$G3, U601.P$G6, U601.P$G7, U601.P$J3, U601.P$J9, X101.GND1, X101.GND2, X101.GND3, X101.GND4, X601.GND1, X601.GND2, X601.GND3, X601.GND4, Y301.2, Y301.4, Y501.2, Y501.4
GND1: J7.SH1, J7.SH2, J7.SH3, J7.SH4, J7.SH5, J7.SH6, J101.P1, J101.P2, J102.P1, J102.P2, J103.P1, J103.P2, J104.P1, J104.P2, J105.P1, J105.P2, J106.P1, J106.P2, J5000.9, R998.2, R999.2
unnamed: C101.2, U101.21
unnamed: C102.1, U101.24
unnamed: C103.1, C104.1, C105.1, JP101.2, U101.1, U101.3, U101.22, U101.23
unnamed: C106.2, C107.2, JP102.2, U102.3, U102.7
unnamed: C108.2, JP103.2, U103.1
unnamed: C109.2, C110.2, JP104.2, U104.8, U104.13
unnamed: C111.1, JP105.1, U106.13
unnamed: C112.1, C113.1, DISP1.10, IC101.3, JP106.2, R101.1
unnamed: C203.1, C204.2, U401.W13
unnamed: C203.2, R204.1, U401.Y13, Y201.1
unnamed: C204.1, R204.2, U401.Y14, Y201.2
unnamed: C301.1, U301.N11, Y301.1
unnamed: C302.1, R305.2, U301.P11, Y301.3
unnamed: C303.1, U301.P9, Y302.1
unnamed: C304.1, U301.N9, Y302.2
unnamed: C305.1, C312.1, C322.1, C330.1, L301.1, TP309.1, U301.F6, U301.F7, U301.F8, U301.F9, U301.G6, U301.G9, U301.H6, U301.H9, U301.J5, U301.J9
unnamed: C309.1, C315.1, Q301.2, TP301.1, U301.N6, U301.P6, U305.6
unnamed: C313.1, TP304.1, U301.M10
unnamed: C314.1, C326.1, TP305.1, U301.P10
unnamed: C316.1, C325.1, TP306.1, U301.P8
unnamed: C317.1, C331.1, D301.2, TP302.1, U301.K8
unnamed: C318.1, D301.1, D302.1, TP303.1, U301.M9
unnamed: C319.1, C324.1, C332.1, L303.2, U301.L1, U301.L2
unnamed: C501.1, U501.N11, Y501.1
unnamed: C502.1, R505.2, U501.P11, Y501.3
unnamed: C503.1, U501.P9, Y502.1
unnamed: C504.1, U501.N9, Y502.2
unnamed: C505.1, C512.1, C522.1, C530.1, L501.1, TP509.1, U501.F6, U501.F7, U501.F8, U501.F9, U501.G6, U501.G9, U501.H6, U501.H9, U501.J5, U501.J9
unnamed: C509.1, C515.1, Q501.2, TP501.1, U501.N6, U501.P6, U505.6
unnamed: C513.1, TP504.1, U501.M10
unnamed: C514.1, C526.1, TP505.1, U501.P10
unnamed: C516.1, C525.1, TP506.1, U501.P8
unnamed: C517.1, C531.1, D501.2, TP502.1, U501.K8
unnamed: C518.1, D501.1, D502.1, TP503.1, U501.M9
unnamed: C519.1, C524.1, C532.1, L503.2, U501.L1, U501.L2
unnamed: C602.1, FB601.2, R604.2
unnamed: D1.1, R1.1
unnamed: D101.1, D102.2, J110.2, Q101.3
unnamed: D101.2, R102.1
unnamed: D102.1, J110.1, J111.1, R102.2
unnamed: D103.2, R108.1
unnamed: D104.2, R109.1
unnamed: D105.2, R110.1
unnamed: D106.2, R111.1
unnamed: D107.2, R112.1
unnamed: D108.2, R113.1
unnamed: D109.2, R114.1
unnamed: D110.2, R115.1
unnamed: D304.1, R302.1
unnamed: D504.1, R502.1
unnamed: D601.1, R601.1
unnamed: D602.1, R603.1
unnamed: D602.2, U601.P$C3
unnamed: DISP1.12, R101.2
unnamed: F301.1, L302.1
unnamed: F501.1, L502.1
unnamed: FB601.1, U601.P$A4, X601.ANTENNA
unnamed: J4.1, R508.2, U401.U7, U401.V7
unnamed: J4.2, R504.2, U401.U8, U401.V8
unnamed: J6.2, U401.M2
unnamed: J7.1, R8.2
unnamed: J301.2, U301.M8
unnamed: J301.3, U301.L8
unnamed: J302.1, U301.H2
unnamed: J302.2, U301.J2
unnamed: J302.3, U301.J4
unnamed: J302.5, U301.J3
unnamed: J302.7, U301.J1
unnamed: J302.8, U301.K1
unnamed: J306.1, U302.10
unnamed: J501.2, U501.M8
unnamed: J501.3, U501.L8
unnamed: J502.1, U501.H2
unnamed: J502.2, U501.J2
unnamed: J502.3, U501.J4
unnamed: J502.5, U501.J3
unnamed: J502.7, U501.J1
unnamed: J502.8, U501.K1
unnamed: J506.1, U502.10
unnamed: JP602.2, U601.P$D4
unnamed: JP602.3, R602.1
unnamed: JP605.2, U601.P$J5
unnamed: JP606.2, U601.P$J4
unnamed: L301.2, U301.M1, U301.M2
unnamed: L302.2, Q301.3
unnamed: L501.2, U501.M1, U501.M2
unnamed: L502.2, Q501.3
unnamed: Q101.1, R103.1, R104.1
unnamed: R205.2, U401.T18
unnamed: R206.2, U401.T19
unnamed: R207.2, U401.T20
unnamed: R208.2, U401.R18
unnamed: R209.2, U401.R19
unnamed: R210.2, U401.R20
unnamed: R211.2, U401.P18
unnamed: R212.2, U401.P19
unnamed: R213.2, U401.P20
unnamed: R214.2, U401.N18
unnamed: R215.2, U401.N19
unnamed: R216.2, U401.N20
unnamed: R217.2, U401.M18
unnamed: R218.2, U401.M19
unnamed: R219.2, U401.M20
unnamed: R220.2, U401.L18
unnamed: R302.2, U302.11
unnamed: R307.2, TP307.1, U301.K7, U305.4
unnamed: R501.2, R503.1, TP1.1, U401.B17
unnamed: R502.2, U502.11
unnamed: R503.2, U1.2
unnamed: R507.2, TP507.1, U501.K7, U505.4
unnamed: SW501.2, U1.3, U401.C17
unnamed: SW502.2, U401.A18
unnamed: TP2.1, U401.D9, U401.D10
unnamed: TP3.1, U401.D13, U401.D14
unnamed: TP4.1, U401.G17, U401.H17
unnamed: TP5.1, U401.J17, U401.K17
unnamed: TP6.1, U401.D11, U401.D12
unnamed: TP7.1, U401.U6
unnamed: TP8.1, U401.U9
unnamed: TP9.1, U401.U10
unnamed: TP10.1, U401.U13
unnamed: TP11.1, U401.M6
unnamed: TP18.1, U401.A19
unnamed: TP201.1, U401.M1
unnamed: U105.1, U105.4, U105.5, U105.6, U105.10, U105.11, U105.15, U105.16, U105.20
unnamed: U106.9, X101.ANTENNA
unnamed: U301.L3, U303.1
unnamed: U301.L4, U303.6
unnamed: U301.N4, U303.5
unnamed: U301.P3, U303.2
unnamed: U301.P4, U303.3
unnamed: U301.P5, U303.7
unnamed: U501.L3, U503.1
unnamed: U501.L4, U503.6
unnamed: U501.N4, U503.5
unnamed: U501.P3, U503.2
unnamed: U501.P4, U503.3
unnamed: U501.P5, U503.7
unnamed: U601.P$J7, Y601.1
unnamed: U601.P$J8, Y601.2

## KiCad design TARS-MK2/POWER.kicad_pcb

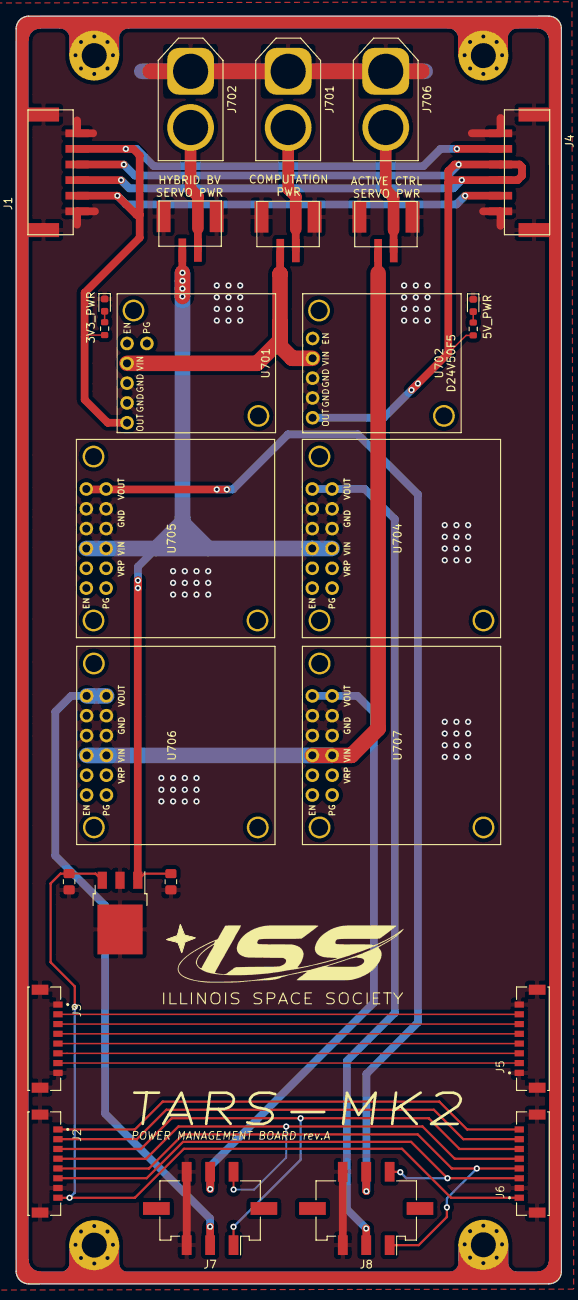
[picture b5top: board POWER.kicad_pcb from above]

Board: 2 copper layers, 69.9 x 162.4 mm, 27 parts (0 on the bottom side), 28 nets.

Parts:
C701, C702: 100nF; C_0805_2012Metric_Pad1.18x1.45mm_HandSolder
D101, D102: LED; LED_0603_1608Metric
J1, J4: 505578-0671
J2, J3, J5, J6: 505567-0871; MOLEX_505567-0871
J7, J8: Conn_02x03_Top_Bottom_MountingPin; Molex_Micro-Fit_3.0_43045-0618_2x03-1MP_P3.00mm_Vertical
J101, J102, J103: 505575-0271
J701, J702, J706: XT60; AMASS_XT60-M_1x02_P7.20mm_Vertical
R101, R102: 1k; R_0603_1608Metric
U701: D36V28F3
U702: D24V50F5
U703: LM7809_TO220; TO-252-3_TabPin2
U704, U705, U706, U707: D36V50F6; D36V50F6-TARS

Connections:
3V3: J1.2, J1.5, J4.2, J4.5, R101.1, U701.5
5V: J1.3, J1.4, J4.3, J4.4, R102.1, U702.5
6V_AC_SERVO1: J7.2, U706.6, U706.12
6V_AC_SERVO2: J7.5, U707.6, U707.12
6V_HYBRID_SERVO3: J8.2, U704.6, U704.12
6V_HYBRID_SERVO4: J8.5, U705.6, U705.12
9V_PT_SUPPLY: C701.1, J2.8, J6.1, U703.3
B2B_SERVO1: J2.3, J6.6, J7.1
B2B_SERVO2: J2.4, J6.5, J7.4
B2B_SERVO3: J2.5, J6.4, J8.1
B2B_SERVO4: J2.6, J6.3, J8.4
GND: C701.2, C702.2, D101.1, D102.1, J1.1, J1.6, J1.P1, J1.P2, J2.7, J2.P1, J2.P2, J3.1, J3.8, J3.P1, J3.P2, J4.1, J4.6, J4.P1, J4.P2, J5.1, J5.8, J5.P1, J5.P2, J6.2, J6.P1, J6.P2, J7.3, J7.6, J8.3, J8.6, J101.3, J101.4, J102.3, J102.4, J103.3, J103.4, J701.1, J702.1, J706.1, U701.3, U701.4, U702.3, U702.4, U703.2, U704.4, U704.5, U704.10, U704.11, U705.4, U705.5, U705.10, U705.11, U706.4, U706.5, U706.10, U706.11, U707.4, U707.5, U707.10, U707.11
unnamed: C702.1, J102.1, U703.1, U704.3, U704.9, U705.3, U705.9
unnamed: D101.2, R101.2
unnamed: D102.2, R102.2
unnamed: J2.1, J6.8
unnamed: J2.2, J6.7
unnamed: J3.2, J5.7
unnamed: J3.3, J5.6
unnamed: J3.4, J5.5
unnamed: J3.5, J5.4
unnamed: J3.6, J5.3
unnamed: J3.7, J5.2
unnamed: J101.1, U701.2, U702.2
unnamed: J101.2, J701.2
unnamed: J102.2, J702.2
unnamed: J103.1, U706.3, U706.9, U707.3, U707.9
unnamed: J103.2, J706.2

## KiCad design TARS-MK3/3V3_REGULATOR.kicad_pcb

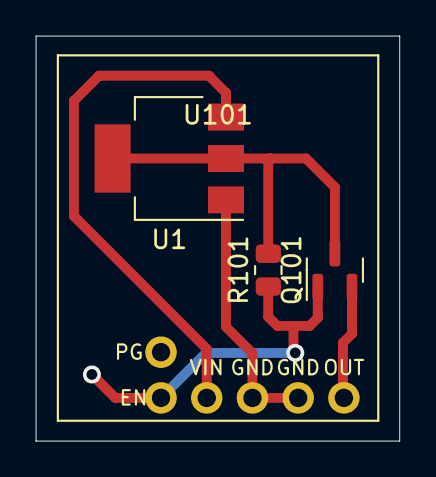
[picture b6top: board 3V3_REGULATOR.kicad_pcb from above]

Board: 2 copper layers, 20.2 x 22.5 mm, 4 parts (0 on the bottom side), 5 nets.

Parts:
Q101: DMG2302U; SOT-23
R101: 10K; R_0805_2012Metric
U1: LD1117S33TR_SOT223; SOT-223-3_TabPin2
U101: D36V28F3; Pololu_3V3_5V_9V

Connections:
/3V3: Q101.2 (S), U101.5 (OUT)
/EN: Q101.1 (G), R101.1, U101.1 (EN)
/IN: U1.3 (VI), U101.2 (VIN)
GND: U1.1 (GND), U101.3 (GND), U101.4 (GND)
unnamed: Q101.3 (D), R101.2, U1.2 (VO)
